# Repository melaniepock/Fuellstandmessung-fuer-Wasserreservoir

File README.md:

# Fuellstandmessung-fuer-Wasserreservoir

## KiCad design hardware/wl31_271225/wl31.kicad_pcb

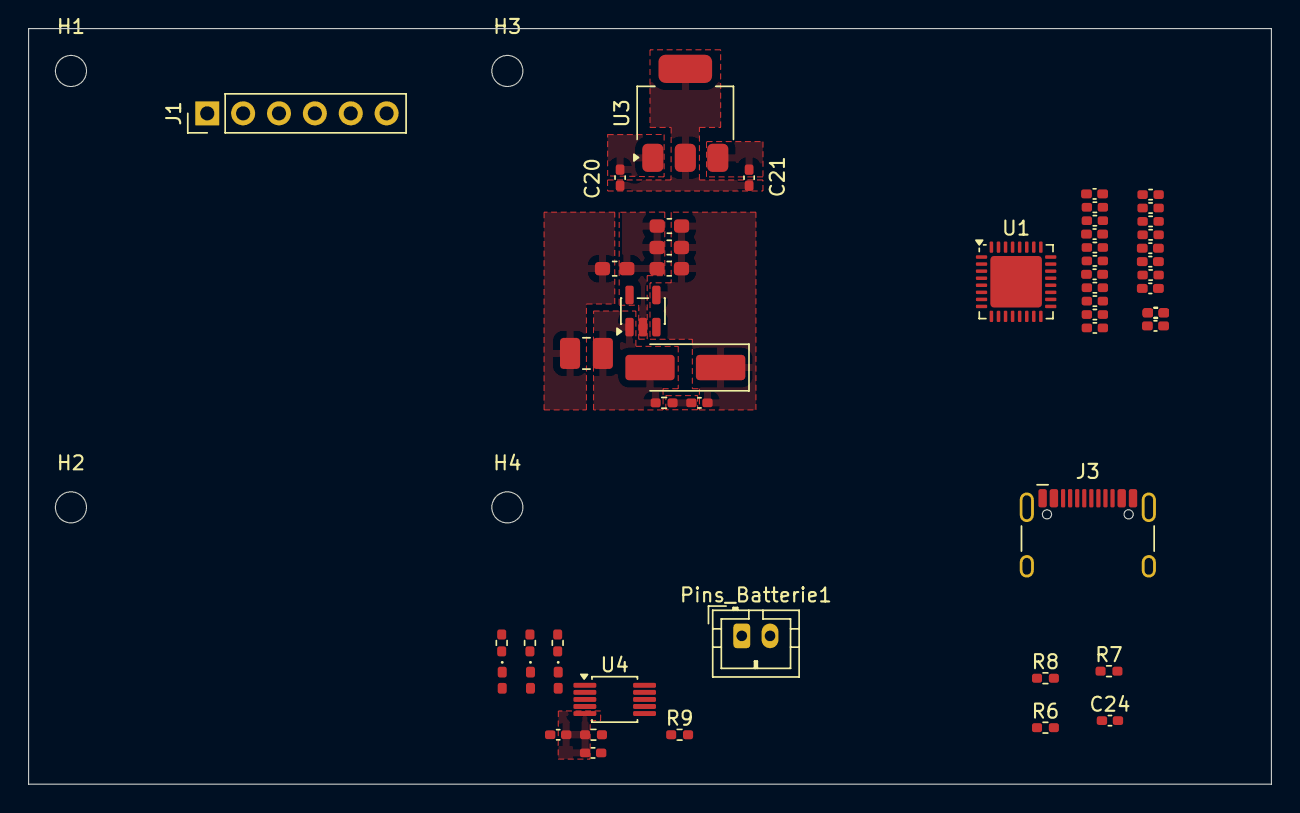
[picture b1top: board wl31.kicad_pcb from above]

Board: 2 copper layers, 88.0 x 53.5 mm, 57 parts (0 on the bottom side), 28 nets.

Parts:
C1, C24: 100nF; C_0402_1005Metric_Pad0.74x0.62mm_HandSolder
C2, C3, C4, C5, C6, C7, C8, C9, C10, C11, C12, C13, C14, C15: C; C_0402_1005Metric_Pad0.74x0.62mm_HandSolder
C16, C18, C19, C25: 10uF; C_0603_1608Metric_Pad1.08x0.95mm_HandSolder
C17: 120pF; C_0402_1005Metric_Pad0.74x0.62mm_HandSolder
C20: 470nF; C_0402_1005Metric_Pad0.74x0.62mm_HandSolder
C21: 33uF; C_0402_1005Metric_Pad0.74x0.62mm_HandSolder
C22, C23: 1uF; C_0402_1005Metric_Pad0.74x0.62mm_HandSolder
D1: D_Schottky; D_SMA_Handsoldering
D2, D3, D4: LED; D_0402_1005Metric_Pad0.77x0.64mm_HandSolder
H1, H2, H3, H4: MountingHole; MountingHole_2.2mm_M2
J1: Conn_01x06_Socket; PinHeader_1x06_P2.54mm_Vertical
J3: USB_C_Receptacle_USB2.0_16P; USB_C_Receptacle_HCTL_HC-TYPE-C-16P-01A
L1, L2, L3, L4, L5, L6, L7: L; L_0402_1005Metric_Pad0.77x0.64mm_HandSolder
L8: 2.2uH; L_1008_2520Metric_Pad1.43x2.20mm_HandSolder
Pins_Batterie1: Conn_01x02_Pin; JST_PH_B2B-PH-K_1x02_P2.00mm_Vertical
R1: 5Ohm; R_0402_1005Metric_Pad0.72x0.64mm_HandSolder
R2, R3, R4: 470Ohm; R_0402_1005Metric_Pad0.72x0.64mm_HandSolder
R5: 1kOhm; R_0402_1005Metric_Pad0.72x0.64mm_HandSolder
R6, R7: 5,1kOhm; R_0402_1005Metric_Pad0.72x0.64mm_HandSolder
R8: 1MOhm; R_0402_1005Metric_Pad0.72x0.64mm_HandSolder
R9: 10kOhm; R_0402_1005Metric_Pad0.72x0.64mm_HandSolder
U1: STM32WL31K8; QFN-32-1EP_5x5mm_P0.5mm_EP3.7x3.7mm
U2: TPS613222ADBV; SOT-23-5
U3: LM3940IMP-3.3; SOT-223
U4: MCP73833-xxx-UN; MSOP-10_3x3mm_P0.5mm

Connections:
/LDO_3.3V: C2.2, C3.2, C4.2, C7.2, C21.1, U1.3 (VDD), U1.19 (VDDRF), U1.25 (VDDSD), U3.3 (OUT)
/Vout_Akku: C23.1, C25.2, L8.1, Pins_Batterie1.2, U4.9 (V_{BAT}), U4.10 (V_{BAT})
/Vout_StepUp: C16.2, C17.2, C18.2, C19.2, C20.1, D1.1 (K), J1.3, U2.4 (VOUT), U3.1 (IN)
/Vout_USBC: C22.1, D2.2 (A), D3.2 (A), D4.2 (A), J3.A4 (VBUS), J3.A9 (VBUS), J3.B4 (VBUS), J3.B9 (VBUS), U4.1 (V_{DD}), U4.2 (V_{DD})
GND: C1.1, C2.1, C3.1, C4.1, C5.1, C6.1, C7.1, C8.2, C9.2, C10.2, C12.2, C14.2, C15.2, C16.1, C18.1, C19.1, C20.2, C21.2, C22.2, C23.2, C24.2, C25.1, J1.1, J3.A1 (GND), J3.A12 (GND), J3.B1 (GND), J3.B12 (GND), Pins_Batterie1.1, R5.1, R6.2, R7.2, R8.1, R9.2, U1.16 (EXTGND), U1.27 (VSSSD), U1.33 (EXP_PAD), U2.2 (GND), U3.2 (GND), U3.4 (GND), U4.5 (V_{SS})
unnamed: C9.1, L4.2, L5.1
unnamed: C10.1, C11.1, L5.2, L6.1
unnamed: C11.2, C12.1, C13.1, L6.2
unnamed: C13.2, C15.1, L7.2
unnamed: C17.1, R1.2
unnamed: D1.2 (A), L8.2, R1.1, U2.1 (SW)
unnamed: D2.1 (K), R2.1
unnamed: D3.1 (K), R3.1
unnamed: D4.1 (K), R4.1
unnamed: J3.A5 (CC1), R6.1
unnamed: J3.B5 (CC2), R7.1
unnamed: C24.1, J3.S1 (SHIELD), R8.2
unnamed: L1.1, L2.2
unnamed: C14.1, L7.1, U1.15 (RX)
unnamed: L3.2, L4.1, U1.17 (TX_HP)
unnamed: C1.2, U1.29 (VCAP)
unnamed: C5.2, C6.2, C8.1, L2.1, L3.1, U1.28 (VFBSD)
unnamed: L1.2, U1.26 (VLXSD)
unnamed: R5.2, U4.6 (PROG)
unnamed: R2.2, U4.3 (STAT1)
unnamed: R3.2, U4.4 (STAT2)
unnamed: R9.1, U4.8 (THERM)
unnamed: R4.2, U4.7 (~PG)

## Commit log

2025-10-25 KiCad Project w/wl31
2025-11-13 KiCad Project wl31
    added holes to attach EvalKit to this PCB
2025-11-26 Power_Supply_Concept
2025-11-26 PSC_neu
    Diode und Enable hinzugefügt für längere Akkulaufzeit
2025-12-11 USB-C, LDO, Ladeschaltung
2025-12-27 Bohrungen und Stiftleiste passen
2025-12-28 Beispiel Datei für Radarmessung
2026-01-02 python API Server mit Testdaten
2026-01-02 ui tabelle + reload button
2026-01-03 auto-refresh hinzugefuegt
2026-01-04 chartjs implementiert
2026-01-04 layout verbesserungen und generell design anpassungen
2026-01-04 warum auch immer, fehlerbehebung
2026-01-04 server.py anpassung war weg
2026-01-06 design verbesserungen
2026-01-07 nur benoetigte sachen von example dringelasse
2026-01-15 uC-Sensor-Kommunikation, funktioniert nicht
2026-02-05 deleted zip
2026-02-05 stm32 example added
2026-02-11 write data in File
2026-02-12 verbesserung bei file
2026-02-15 nach Datum filtern jetzt möglich
2026-02-15 Ausbesserung
2026-02-17 hacked firmware so that we INIT command results in a valid response
2026-02-26 checkin of imported Altium reference design
2026-02-26 old kicad project for 9.0
2026-02-26 added components of old project
2026-03-18 old components in pcb-layout
2026-03-21 neuer Server Zwischenstand
2026-03-22 gitignore hinzugefügt
2026-03-22 jetzt richtige version von gitignore
2026-03-22 neuerserver.py mit 'simulation' und config und neuem datumsformat und supabase
2026-03-22 aktuellere Daten in Test csv
2026-03-22 supabase und werte - höhe berechnung
2026-04-28 latest
